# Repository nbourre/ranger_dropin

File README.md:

# Ranger drop-in: BEAPER Nano carrier for ESP32-S3

Goal: replace the Arduino-based **Makeblock Auriga** controller of an mBot Ranger with a custom carrier board for an **ESP32-S3-DevKitC-1-N16R8**, based on the mirobo.tech **BEAPER Nano** schematic converted to SMD parts (JLCPCB/LCSC, Basic parts where possible).

Project files: KiCad 10 (`Beaper-Esp32s3.kicad_sch`, `Beaper-Esp32s3.kicad_pcb`), custom footprint library `BEAPER-Nano.pretty`, custom symbol library `ESP32S3.kicad_sym`. Reference: `auriga/Me Auriga Schematic.pdf`.

> **Status (2026-10-22):** schematic and PCB are in sync (127 footprints, all on the top side so the board clips into the robot). **Placement is done; routing, ground pours and the final DRC are still to do.** See `memoire/notes-a-faire.md` for the layout, the decisions and the task list, and `memoire/MEMOIRE.md` for the working notes (Konnect MCP tips). Photos of the Auriga are in `auriga/photos/`; extra 3D models are in `3dmodels/`.

---

## 1. Makeblock Auriga (original controller)

Source: `auriga/Me Auriga Schematic.pdf` (one page, read as text). Items marked *(memory)* are not visible in that PDF and come from general knowledge of the mBot Ranger. The full pin-by-pin map is in [AURIGA_PINMAP.md](AURIGA_PINMAP.md).

**Board size (measured): 65.5 × 100 mm, corner radius 2 mm** (target outline for the drop-in PCB). The original has no mounting holes (clipped in).

| Function | Details |
|---|---|
| MCU | ATmega2560 *(memory)*, with ICSP header |
| USB-serial | CH340G |
| Motor driver | TB6612 (1.2 A continuous per channel), two motor ports with encoders (`ENC` signals, 51 Ω series resistors) |
| Motor power protection | Fuses (1 A per motor, 3.5 A main), SS54 diode, SMAJ TVS, 470 µF / 16 V on the motor rail |
| Regulators | 5 V LDO and 3.3 V XC6206 |
| IMU | MPU6050 gyroscope + accelerometer (I2C, INT and AD0 pins) |
| RGB LED ring | 12 RGB LEDs, one data line (`D44/RGB`) |
| Ambient light sensors | LIGHT1 and LIGHT2 |
| Sound sensor | Microphone with LM2904 amplifier |
| Temperature sensor | Present (`TEMP`) |
| Buzzer | Present |
| User button | One (`KEY`) |
| Status LEDs | LED_RED, LED_BLUE |
| RJ25 ports | 10 ports for Makeblock modules (line follower, ultrasonic, etc.) |
| Servo header | `P_SERVO`, powered from the motor rail (V-M) |
| Wireless | Bluetooth / 2.4 G module socket *(memory)* |

---

## 2. BEAPER Nano on ESP32-S3 (this project)

Carrier board for the ESP32-S3-DevKitC-1-N16R8 (U5, two 22-pin headers, 22.86 mm apart).

### Power
- Battery input on **J1** (5.5 × 2.1 mm DC barrel jack, centre = VBAT), 7.2 V NiMH RC pack. The old screw terminal CON1 was removed.
- Protection: the battery (net `VBAT`, SMAJ13A TVS D9) splits into two fused branches, as on the Auriga. **Motor branch:** fuse F1 (3.5 A), SS54 diode D8, 470 µF bulk capacitor C8, net `VCC` (TB6612 VM, battery sense, panel V-BAT). **Logic branch:** fuse F2 (3 A, C182445), SS34 diode D13, then the buck U1. A motor stall that blows F1 therefore leaves the logic and servos powered.
- **U1 (TPS54331DDA, 3 A buck, LCSC C90761)** makes the +5 V rail, as on the Auriga (L1 6.8 µH, D10 SS34, 10 k / 1.91 k feedback divider, 470 µF output capacitor). D11 (SS34) isolates the buck from the +5 V rail so that USB power cannot back-feed it (the rail is about 4.7 V), and D12 (SMAJ5.0A) clamps the rail. The DevKitC-1 has no VIN pin, so it is powered through its 5V pin. U1 is therefore **required**.
- 3.3 V comes from the DevKitC-1.
- No on-board USB charger (external charger for the pack).

### Motors
- **U3 TB6612FNG** (SSOP-24, LCSC C141517, Extended part). Replaces the SN754410 of the original design.
- Motor outputs are protected like on the Auriga: TB6612 output → bidirectional TVS SMAJ12CA (D14 to D17) → 120 Ω / 2 A ferrite bead (FB1 to FB4) → 1 A PTC fuse (F3 to F6) → connector.
- **M1 and M2** are **JST PH 6-pin side-entry connectors (2.0 mm pitch, S6B-PH-K)**, as on the Auriga (see `auriga/photos/`): pin 6 motor+, 5 motor−, 4 GND, 3 +3V3, 2 encoder A, 1 encoder B. Pin 1 orientation still has to be checked on a real motor plug.
- Encoder signals go through 51 Ω resistors (R31 to R34) to GPIO 39 to 42. Encoders are powered at **3.3 V** (the Auriga uses 5 V). To be tested with the real motors.
- Difference from the old driver: with both inputs low, the TB6612 coasts (the SN754410 braked). Maximum supply: 13.5 V.

### Sensors and I/O
- **U6 LSM6DS3TR-C** (LCSC C967633): 6-axis IMU on I2C (address 0x6A), interrupts not connected.
- **Battery voltage monitor** (`VOL_BAT`, like the Auriga's A4/VOL_BAT): R35 100 kΩ / R36 51 kΩ divider + C11 1 µF on **GPIO 3** (ADC1_CH2). Ratio 0.338, so a 9 V pack reads about 3.0 V. It is tapped after D8, so it reads about 0.4 V low: calibrate in firmware. GPIO 3 is a strapping pin, which only matters at reset.
- Ambient light sensor (TEPT4400) removed; the Auriga's light module will be reused instead (see TODO).
- Temperature sensor (MCP9700A, on A1), wired directly (no selection jumpers).
- Line / floor sensors and potentiometers were **removed** to free GPIO. As on the Auriga, line-following is done by an external I2C module (home-made: Adafruit ATtiny1616 with seesaw firmware, sensors wired to the ATtiny) on the Qwiic connector (J4) or H1/H4.
- Headers H1 (A4 / SDA) and H4 (A5 / SCL): I2C signals at 3.3 V. The sonar headers H2/H3 were removed.
- Headers H7 (A6 / GPIO 6) and H8 (A7 / GPIO 7): 5 V servo outputs through the **74HCT541** level shifter (U2) for the pan/tilt micro servos (H5/H6 removed). Generate the servo PWM with LEDC.
- I2C expansion on the main 3.3 V bus: two Qwiic / JST-SH connectors (J4, J8) and three generic 4-pin headers (J9, J15, J16: GND, +3V3, SCL, SDA). SPI / TFT connector (J3).
- Piezo buzzer (LS1), 4 status LEDs (D2 to D5), reset button (SW1).

### GPIO mapping (Arduino-style net name → ESP32-S3 GPIO)

| Net | GPIO | Net | GPIO |
|---|---|---|---|
| PA_S1 (RJ25 A) | 1 | D5 | 17 |
| A1 | 2 | D6 | 18 |
| A2 (LIGHT2) | 4 | D7 | 21 |
| A3 (LIGHT1) | 5 | D8 (buzzer) | 47 |
| A6 | 6 | D9 (J3, RJ25 C) | 38 |
| A7 | 7 | D10 (J3, RJ25 C) | 10 |
| A4/SDA | 8 | D11/COPI | 11 |
| A5/SCL | 9 | D12/CIPO | 13 |
| PB_S2 (RJ25 B) | 44 | D13/SCK | 12 |
| PB_S1 (RJ25 B) | 43 | ~{RST} (SW1) | EN |
| KEY_GPIO | 14 | Encoders | 39, 40, 41, 42 |
| PA_S2 (RJ25 A) | 15 | RGB_3V3 (ring data) | 48 |
| D4 | 16 | VOL_BAT | 3 |

No free GPIO is left. **45, 46, 0** are strapping pins (unused, usable with care). **19, 20** are USB D−/D+. **35, 36, 37** are used by the octal PSRAM and must stay unused. GPIO 43/44 are the UART0 pins of the DevKitC-1 USB-UART bridge: a module on RJ25 port B may conflict while that USB port is connected.

### Panel module, RJ25, Qwiic and expansion connectors
- **J12** PRGB (female 1x7, left to right): V-BAT (`VCC`), KEY, A2/LIGHT2, A3/LIGHT1, RGB, GND, 5 V. **J13, J14**: female 1x2 GND supports.
- **KEY** is active high: the module button ties KEY to V-BAT (measured with a multimeter). R38 15k / R37 10k to GND divide it to under 3.4 V on GPIO 14. Configure GPIO 14 as input with no internal pull-up.
- **RGB ring data:** GPIO 48 → U7 74AHCT1G125 (3.3 V → 5 V buffer) → R39 220 Ω → J12.5.
- **J5, J6, J7** RJ25 (Amphenol 54601-906WPLF, 6P6C), low-power side only: 1 SCL, 2 SDA, 3 GND, 4 +5 V, 5 S1, 6 S2. They behave like the Auriga ports (**5 V**): the six S1/S2 signals go through BSS138 level shifters (Q3 to Q8, 10 k pull-ups R45 to R56), and the port supply is `5V_P` (buck output before D11). The RJ25 I2C bus (EXT_SCL / EXT_SDA, through Q1/Q2) has its pull-ups on 3.3 V or 5 V, selected with **JP1** (1-2 = 3.3 V, 2-3 = 5 V, Makeblock setting). Digital only (no 0–5 V analog); port B uses GPIO 43/44 (UART0); port C shares D9/D10 with the SPI header J3. The jacks have the contacts on top (the Auriga's are at the bottom): the cable just has to be twisted, the pinout is the same.
- **J4, J8** Qwiic (JST-SH 4-pin: GND, 3V3, SDA, SCL); **J9, J15, J16** generic I2C headers.
- **J10** VL53L1X module (Amazon board, silkscreen order): 1 VIN (3.3 V), 2 GND, 3 SCL, 4 SDA, 5 GPIO1 (not connected), 6 XSHUT (not connected). On placement it must point the same way as the Auriga motor connectors.
- **J11** OLED I2C socket, assumed order GND, 3V3, SCL, SDA (module not yet chosen, to confirm).

---

## 3. Comparison

### On the Auriga but missing on the new board
- 12-LED ring itself and the light sensors: the Auriga **panel module is reused** through J12 to J14 (the ring data line is level-shifted from GPIO 48).
- Microphone and amplifier.
- Power switch.
- RJ25 ports: only 3 low-power ports (J5 to J7) are provided, no motor-power side.
- Dedicated Bluetooth / 2.4 G socket. Wi-Fi and BLE are built into the ESP32-S3.

### On the new board but not on the Auriga
- SPI / TFT connector (J3).
- Qwiic / JST-SH I2C connectors (J4, J8) and generic I2C headers (J9, J15, J16).
- VL53L1X module socket (J10) and OLED I2C socket (J11).
- I2C headers H1 / H4 (3.3 V) and servo headers H7 / H8 (5 V outputs).
- Onboard user buttons were removed; the user button is planned on the panel module `KEY` pin (see TODO).
- Four simple status LEDs.
- Wi-Fi and BLE through the ESP32-S3, with native USB.

### In both
Buzzer, temperature sensor, IMU, battery voltage sensing, motors with encoders, battery protection, reset button, servo outputs.

---

## 4. Open items
- **5 V supply:** done. The LM2940 was replaced by a TPS54331 3 A buck, and C7 (470 µF) sits near the servo headers. Use 5 V micro servos (9 g) and generate the servo signals with LEDC. The buck has its own fuse F2 and reverse diode D13, separate from the motor fuse F1. The motor outputs have their own TVS, ferrite and 1 A PTC fuse (done).
- The DevKitC-1 footprint outline is approximate (pad envelope only), and it has no 3D model yet.
- Missing LCSC references: F1, D8, D9, C8 (470 µF probably not stocked), R31 to R36, R45 to R56, C9 to C12, M1/M2 (S6B-PH-K-S), U7, RJ25, Qwiic. The 5.62 kΩ and 1.37 kΩ resistors are Extended only.
- Routing, ground pours, silkscreen clean-up and the final DRC are not done. The motor lines are long (U3 near the top, M1/M2 at the bottom edge).
- Missing 3D models: L1 (Bourns SRP7028A), SW1 (Alps SKRTLAE010), U5, G1. The RJ25 model is in `3dmodels/`.
- Optional additions to match the Auriga: power switch.
- The title block comment 3 still says "for Arduino Nano ESP32".
- The schematic page was enlarged from B to C to make room for the IMU.
- ERC: 0 errors, 58 warnings (library symbol mismatches, missing `Conn_01x03_Male`, `ARPS` and `UBMP4.1-rescue` libraries, same local/global label names, one U6 SDO pin type conflict). Leftover wires, orphan power symbols and floating labels were cleaned.

---

## 5. TODO
- [x] **Distance sensor** VL53L1X: socket J10 on the I2C bus (Amazon module, order VIN, GND, SCL, SDA, GPIO1, XSHUT; last two not connected). Must face the same way as the Auriga motor connectors at placement.
- [x] **Auriga panel module** (RGB ring + light sensors): J12 (1x7 female), J13/J14 (1x2 GND supports), level-shifted data (U7). See `AURIGA_PINMAP.md` for the geometry to reproduce at placement (module 36.1 × 50 mm, GND headers 31.75 mm apart).
- [x] Panel KEY used as the general button (active high, divider to GPIO 14). Board buttons SW2 to SW5 removed.
- [x] 3 RJ25 ports (low-power side, 5 V with level shifters), 2 Qwiic connectors and 3 generic I2C headers.
- [x] PCB outline (65.5 × 100 mm, R2) and the three Ø 2 mm guide holes.
- [x] `update_pcb_from_schematic` and component placement (everything on the top side).
- [ ] Routing, ground pours, silkscreen clean-up, final ERC / DRC, 3D check.
- [ ] **Mount the DevKit (U5) on "double" female headers: 2x22 instead of 1x22 per side.** One row receives the DevKit pins, the parallel extra row (wired pin to pin, preferably on the outer side) gives access to every DevKit pin for measurements, jumper wires and other DevKit variants. Likely a custom U5 footprint with two pads per pin number. Check the width (22.86 mm + 2 × 2.54 mm on a 65.5 mm board), the neighbours (J3, J11, the H column) and the height budget under the panel module (about 8.5 mm). Do this first: it makes the next item mostly unnecessary.
- [ ] **Breakout header for GPIO 35, 36 and 37.** These pins are reserved by the **octal PSRAM** ("R8" variants: N16R8, N8R8), whatever the flash size. They are free on variants without octal PSRAM that share the same footprint (N8R2 with quad PSRAM, N8 / N4 without PSRAM), so a 1x03 header would only be useful with one of those (to be confirmed against the Espressif module datasheet). Label it on the silkscreen ("without octal PSRAM only") and update the GPIO table if used.
- [ ] Confirm the OLED module pinout (J11 is an assumed order).
- [ ] LCSC references for the new parts (connectors, U7, R37 to R39, C12).
- [ ] Line-follower I2C module (home-made, Adafruit ATtiny1616 with seesaw, address 0x49) on a Qwiic connector. Source: `nbourre/LyneTracker` (target ATmega2560; porting only needs the I2C pins GPIO 8/9, 3.3 V). Check pull-ups and supply at 3.3 V.
- [ ] **Makeblock mounting holes:** nominally 8 mm pitch, M4; measure on a real beam.

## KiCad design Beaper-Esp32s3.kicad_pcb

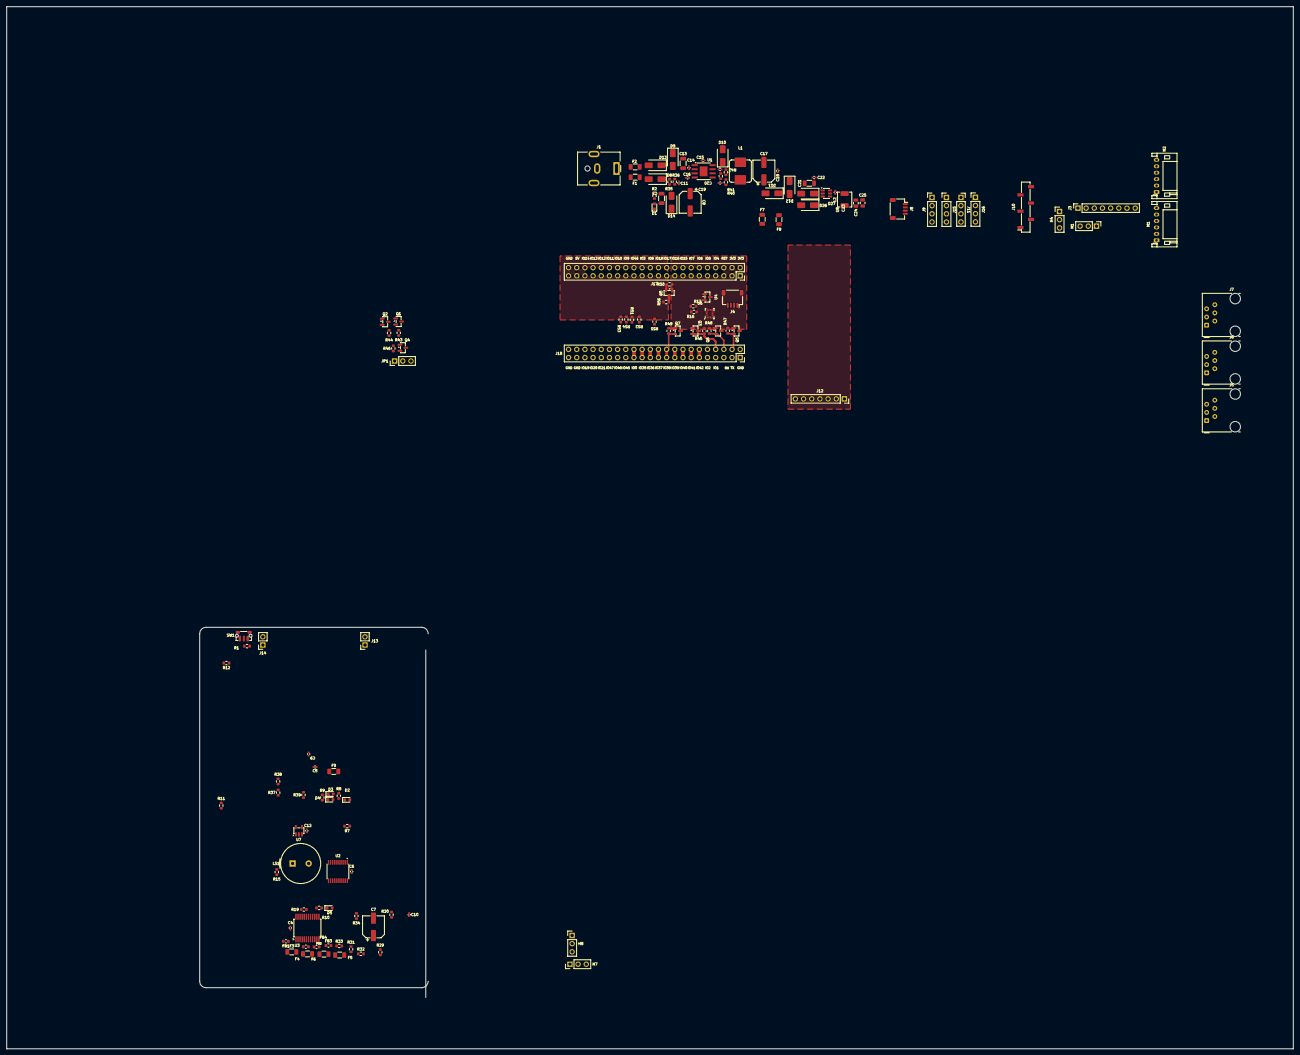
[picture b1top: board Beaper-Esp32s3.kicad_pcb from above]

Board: 2 copper layers, 399.9 x 323.9 mm, 133 parts (0 on the bottom side), 104 nets.

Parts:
C3, C13, C21: 10uF/50V; C_1206_3216Metric
C4, C5, C6, C9, C10, C12, C14, C15, C18, C22, C23: 100nF; C_0402_1005Metric
C7, C8: 470uF/16V; CP_Elec_6.3x7.7
C11: 1uF; C_0402_1005Metric
C16: 10nF; C_0402_1005Metric
C17: 470uF; CP_Elec_6.3x7.7
C19: 120pF; C_0402_1005Metric
C20: 68pF; C_0402_1005Metric
C24, C25: 22uF/10V; C_0805_2012Metric
D1: Vin; LED_0603_1608Metric
D2, D3, D4, D5: LED; LED_0603_1608Metric
D8, D10, D11: SS54; D_SMA
D9: SMAJ13CA; D_SMA
D12: SMAJ5.0CA; D_SMA
D13, D26, D27: SS34; D_SMA
D14: SMAJ10CA; D_SMA
F1: 4A T; Fuse_1206_3216Metric
F2: 3A; Fuse_1206_3216Metric
F3, F4, F5, F6, F9: 1A PTC; Fuse_1206_3216Metric
F7: 1.5A PTC; Fuse_1206_3216Metric
F8: 1.1A PTC; Fuse_1206_3216Metric
FB1, FB2, FB3, FB4: 120R/2A; L_0603_1608Metric
H1: A4 (SDA); PinHeader_1x03_P2.54mm_Vertical
H4: A5 (SCL); PinHeader_1x03_P2.54mm_Vertical
H7: A6 (Servo 3); PinHeader_1x03_P2.54mm_Vertical
H8: A7 (Servo 4); PinHeader_1x03_P2.54mm_Vertical
J1: PJ-063AH 8A (2,0 mm); BarrelJack_CUI_PJ-063AH_Horizontal
J3: Conn_01x08; PinSocket_1x08_P2.54mm_Vertical
J4, J8: QWIIC/JST SH; JST_SH_SM04B-SRSS-TB_1x04-1MP_P1.00mm_Horizontal
J5: RJ25 port A; RJ12_Amphenol_54601-x06_Horizontal
J6: RJ25 port B; RJ12_Amphenol_54601-x06_Horizontal
J7: RJ25 port C; RJ12_Amphenol_54601-x06_Horizontal
J9, J15, J16: I2C (GND 3V3 SCL SDA); PinHeader_1x04_P2.54mm_Vertical
J10: VL53L1X module; PinSocket_1x06_P2.54mm_Vertical_SMD_Pin1Right
J11: OLED I2C; PinSocket_1x04_P2.54mm_Vertical
J12: PRGB (Auriga panel module); PinSocket_1x07_P2.54mm_Vertical
J13: PG1 (GND support); PinSocket_1x02_P2.54mm_Vertical
J14: PG2 (GND support); PinSocket_1x02_P2.54mm_Vertical
J17: Socket 2x22 (U5 L1-L22); PinSocket_2x22_P2.54mm_Vertical
J18: Socket 2x22 (U5 R1-R22); PinSocket_2x22_P2.54mm_Vertical
JP1: I2C EXT 3V3/5V; PinHeader_1x03_P2.54mm_Vertical
L1: 6.8uH/4.5A; L_Bourns_SRP7028A_7.3x6.6mm
L2: 3.9uH; L_Sunlord_MWSA0412S
LS1: Piezo Beeper; Buzzer_TDK_PS1240P02BT_D12.2mm_H6.5mm
M1: Moteur 1 (MHDR1X6); JST_PH_S6B-PH-K_1x06_P2.00mm_Horizontal
M2: Moteur 2 (MHDR1X6); JST_PH_S6B-PH-K_1x06_P2.00mm_Horizontal
Q1, Q2, Q3, Q4, Q5, Q6, Q7, Q8: BSS138; SOT-23
R1: 100; R_0603_1608Metric
R2, R15: 1k0; R_0603_1608Metric
R7, R8, R9, R10: 270; R_0603_1608Metric
R11, R12: 150; R_0603_1608Metric
R16, R17: 4k7; R_0603_1608Metric
R19, R37, R45, R46, R47, R48, R49, R50, R51, R52, R53, R54, R55, R56: 10k; R_0603_1608Metric
R29, R30: 470; R_0603_1608Metric
R31, R32, R33, R34: 51; R_0603_1608Metric
R35: 100k; R_0603_1608Metric
R36: 51k; R_0603_1608Metric
R38: 15k; R_0603_1608Metric
R39: 330; R_0603_1608Metric
R40: 27k; R_0603_1608Metric
R41: 5.1k; R_0603_1608Metric
R42: 30k; R_0603_1608Metric
R43, R44: 4.7k; R_0603_1608Metric
SW1: RESET; SW_Push_1P1T-MP_NO_Horizontal_Alps_SKRTLAE010
U1: TPS54331DDA; TI_SO-PowerPAD-8
U2: 74HCT541; TSSOP-20_4.4x6.5mm_P0.65mm
U3: TB6612FNG; SSOP-24_5.3x8.2mm_P0.65mm
U4: MCP9700AT-E/TT; SOT-23
U6: LSM6DSOTR; LGA-14_3x2.5mm_P0.5mm_LayoutBorder3x4y
U7: 74AHCT1G125; SOT-23-5
U8: AP63203WU; TSOT-23-6

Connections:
+3V3: C5.1, C9.1, C10.1, J4.2, J17.1, J17.2, J17.3, J17.4, JP1.1, Q1.1 (G), Q2.1 (G), Q3.1 (G), Q4.1 (G), Q5.1 (G), Q6.1 (G), Q7.1 (G), Q8.1 (G), R16.1, R17.1, R45.2, R46.2, R47.2, R48.2, R49.2, R50.2, U4.1 (V_{DD}), U6.5 (VDDIO), U6.8 (VDD), U6.12 (CS)
+3V3_EXT: C24.1, C25.1, H1.2, H4.2, J3.2, J8.2, J9.2, J10.1, J11.2, J15.2, J16.2, L2.2, M1.3, M2.3, U8.1 (FB)
+5V: C4.1, C6.1, C12.1, D11.1 (K), D12.2 (A2), D27.2 (A), F7.1, F8.1, J17.41, J17.42, JP1.3, R19.1, R51.1, R52.1, R53.1, R54.1, R55.1, R56.1, U2.20 (VCC), U3.15 (PWMB), U3.20 (VCC), U3.23 (PWMA), U7.5 (VCC)
+5V_EXT: F8.2, J5.4, J6.4, J7.4, J12.7
+5V_SERVO: C7.1, F7.2, H7.2, H8.2
/A1: J18.9, J18.10, U4.2 (V_{OUT})
/A2: J12.3, J17.7, J17.8
/A3: J12.4, J17.9, J17.10
/A4/SDA: J4.3, J8.3, J9.4, J10.4, J11.4, J15.4, J16.4, J17.23, J17.24, Q1.2 (S), R11.2, R16.2, U2.5 (A3), U6.14 (SDA)
/A5/SCL: J4.4, J8.4, J9.3, J10.3, J11.3, J15.3, J16.3, J17.29, J17.30, Q2.2 (S), R12.2, R17.2, U2.4 (A2), U6.13 (SCL)
/A6: J17.11, J17.12, U2.3 (A1)
/A7: J17.13, J17.14, U2.2 (A0)
/BUCK_BST: C23.1, U8.6 (BST)
/BUCK_SW: C23.2, L2.1, U8.5 (SW)
/D4: J17.17, J17.18, R7.1, U2.6 (A4)
/D5: J17.19, J17.20, R8.1, U2.7 (A5)
/D6: J17.21, J17.22, R9.1, U2.8 (A6)
/D7: J18.35, J18.36, R10.1, U2.9 (A7)
/D8: J18.33, J18.34, LS1.1, R15.2
/D9: J3.6, J18.19, J18.20, Q7.2 (S), R49.1
/D10: J3.7, J17.31, J17.32, Q8.2 (S), R50.1
/D11/COPI: J3.4, J17.33, J17.34
/D12/CIPO: J3.8, J17.37, J17.38
/D13/SCK: J3.3, J17.35, J17.36
/ENC1A: J18.17, J18.18, R31.2
/ENC1A_H: M1.2, R31.1
/ENC1B: J18.15, J18.16, R32.2
/ENC1B_H: M1.1, R32.1
/ENC2A: J18.13, J18.14, R33.2
/ENC2A_H: M2.2, R33.1
/ENC2B: J18.11, J18.12, R34.2
/ENC2B_H: M2.1, R34.1
/EXT_SCL: J5.1, J6.1, J7.1, Q2.3 (D), R44.2
/EXT_SDA: J5.2, J6.2, J7.2, Q1.3 (D), R43.2
/FB: R40.2, R41.1, U1.5 (VSENSE)
/IMU_INT1: J17.27, J17.28, U6.4 (INT1)
/KEY: J12.2, R38.1
/KEY_GPIO: J17.39, J17.40, R37.2, R38.2
/M1A: F3.2, M1.6
/M1A_D: FB1.1, U3.1 (AO1), U3.2 (AO1)
/M1B: F4.2, M1.5
/M1B_D: FB2.1, U3.5 (AO2), U3.6 (AO2)
/M1_IN1: U2.14 (Y4), U3.21 (AIN1)
/M1_IN2: U2.13 (Y5), U3.22 (AIN2)
/M2A: F5.2, M2.6
/M2A_D: FB3.1, U3.11 (BO1), U3.12 (BO1)
/M2B: F6.2, M2.5
/M2B_D: FB4.1, U3.7 (BO2), U3.8 (BO2)
/M2_IN1: U2.12 (Y6), U3.17 (BIN1)
/M2_IN2: U2.11 (Y7), U3.16 (BIN2)
/MOTOR_STBY: R19.2, U3.19 (STBY)
/PA_S1: J18.7, J18.8, Q3.2 (S), R45.1
/PA_S1_5V: J5.5, Q3.3 (D), R51.2
/PA_S2: J17.15, J17.16, Q4.2 (S), R46.1
/PA_S2_5V: J5.6, Q4.3 (D), R52.2
/PB_S1: J18.3, J18.4, Q5.2 (S), R47.1
/PB_S1_5V: J6.5, Q5.3 (D), R53.2
/PB_S2: J18.5, J18.6, Q6.2 (S), R48.1
/PB_S2_5V: J6.6, Q6.3 (D), R54.2
/PC_S1_5V: J7.5, Q7.3 (D), R55.2
/PC_S2_5V: J7.6, Q8.3 (D), R56.2
/RGB: J12.5, R39.2
/RGB_3V3: J18.31, J18.32, U7.2
/RGB_BUF: R39.1, U7.4
/VBAT_IN: F1.2, F2.1, J1.1
/VBUCK: C21.1, C22.1, D26.1 (K), D27.1 (K), U8.2 (EN), U8.3 (IN)
/VI2C: JP1.2, R43.1, R44.1
/VOL_BAT: C11.1, J17.25, J17.26, R35.2, R36.1
/~RST: J3.5, J17.5, J17.6, R1.2
GND: C3.2, C4.2, C5.2, C6.2, C7.2, C8.2, C9.2, C10.2, C11.2, C12.2, C13.2, C14.2, C16.2, C17.2, C18.2, C19.2, C20.2, C21.2, C22.2, C24.2, C25.2, D1.1 (K), D2.1 (K), D3.1 (K), D4.1 (K), D5.1 (K), D9.1 (A1), D10.2 (A), D12.1 (A1), D14.1 (A1), H1.3, H4.3, H7.3, H8.3, J1.2, J3.1, J4.1, J5.3, J6.3, J7.3, J8.1, J9.1, J10.2, J11.1, J12.6, J13.1, J13.2, J14.1, J14.2, J15.1, J16.1, J17.43, J17.44, J18.1, J18.2, J18.41, J18.42, J18.43, J18.44, LS1.2, M1.4, M2.4, R15.1, R36.2, R37.1, R41.2, SW1.1, U1.7 (GND), U1.9 (PowerPAD), U2.1 (G1), U2.10 (GND), U2.19 (G2), U3.3 (PGND1), U3.4 (PGND1), U3.9 (PGND2), U3.10 (PGND2), U3.18 (GND), U4.3 (GND), U6.1 (SDO/SA0), U6.2 (SDX), U6.3 (SCX), U6.6 (GND), U6.7 (GND), U7.1, U7.3 (GND), U8.4 (GND)
unnamed: C19.1, R42.2
unnamed: D1.2 (A), R2.1
unnamed: D2.2 (A), R7.2
unnamed: D3.2 (A), R8.2
unnamed: D4.2 (A), R9.2
unnamed: D5.2 (A), R10.2
unnamed: D8.2 (A), F1.1
unnamed: C15.2, D10.1 (K), L1.1, U1.8 (PH)
unnamed: C17.1, C18.1, D11.2 (A), L1.2, R40.1
unnamed: D13.2 (A), F2.2
unnamed: C13.1, C14.1, D9.2 (A2), D13.1 (K), U1.2 (VIN)
unnamed: F3.1, FB1.2
unnamed: F4.1, FB2.2
unnamed: F5.1, FB3.2
unnamed: F6.1, FB4.2
unnamed: H1.1, R11.1
unnamed: H4.1, R12.1
unnamed: H7.1, R29.1
unnamed: H8.1, R30.1
unnamed: J18.21, J18.22
unnamed: J18.23, J18.24
unnamed: J18.25, J18.26
unnamed: J18.27, J18.28
unnamed: J18.29, J18.30
unnamed: J18.37, J18.38
unnamed: J18.39, J18.40
unnamed: R1.1, SW1.2
unnamed: C15.1, U1.1 (BOOT)
unnamed: C20.1, R42.1, U1.6 (COMP)
unnamed: C16.1, U1.4 (SS/TR)
unnamed: R30.2, U2.18 (Y0)
unnamed: R29.2, U2.17 (Y1)
VCC: C3.1, C8.1, D8.1 (K), D14.2 (A2), D26.2 (A), F9.1, R2.2, R35.1, U3.13 (VM2), U3.14 (VM3), U3.24 (VM1)
VCC_EXT: F9.2, J12.1

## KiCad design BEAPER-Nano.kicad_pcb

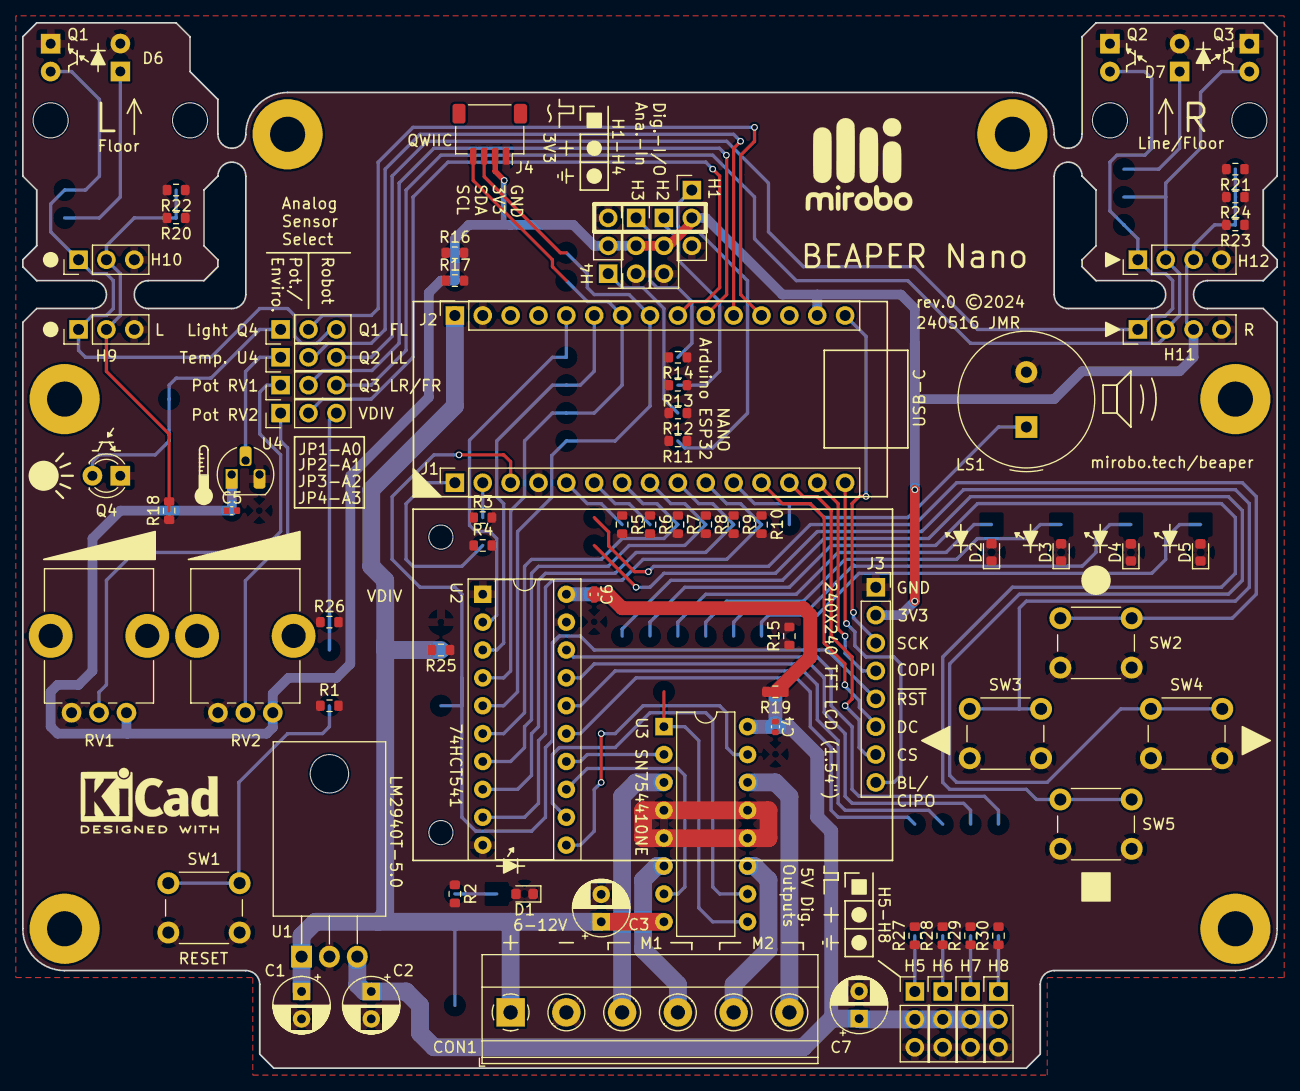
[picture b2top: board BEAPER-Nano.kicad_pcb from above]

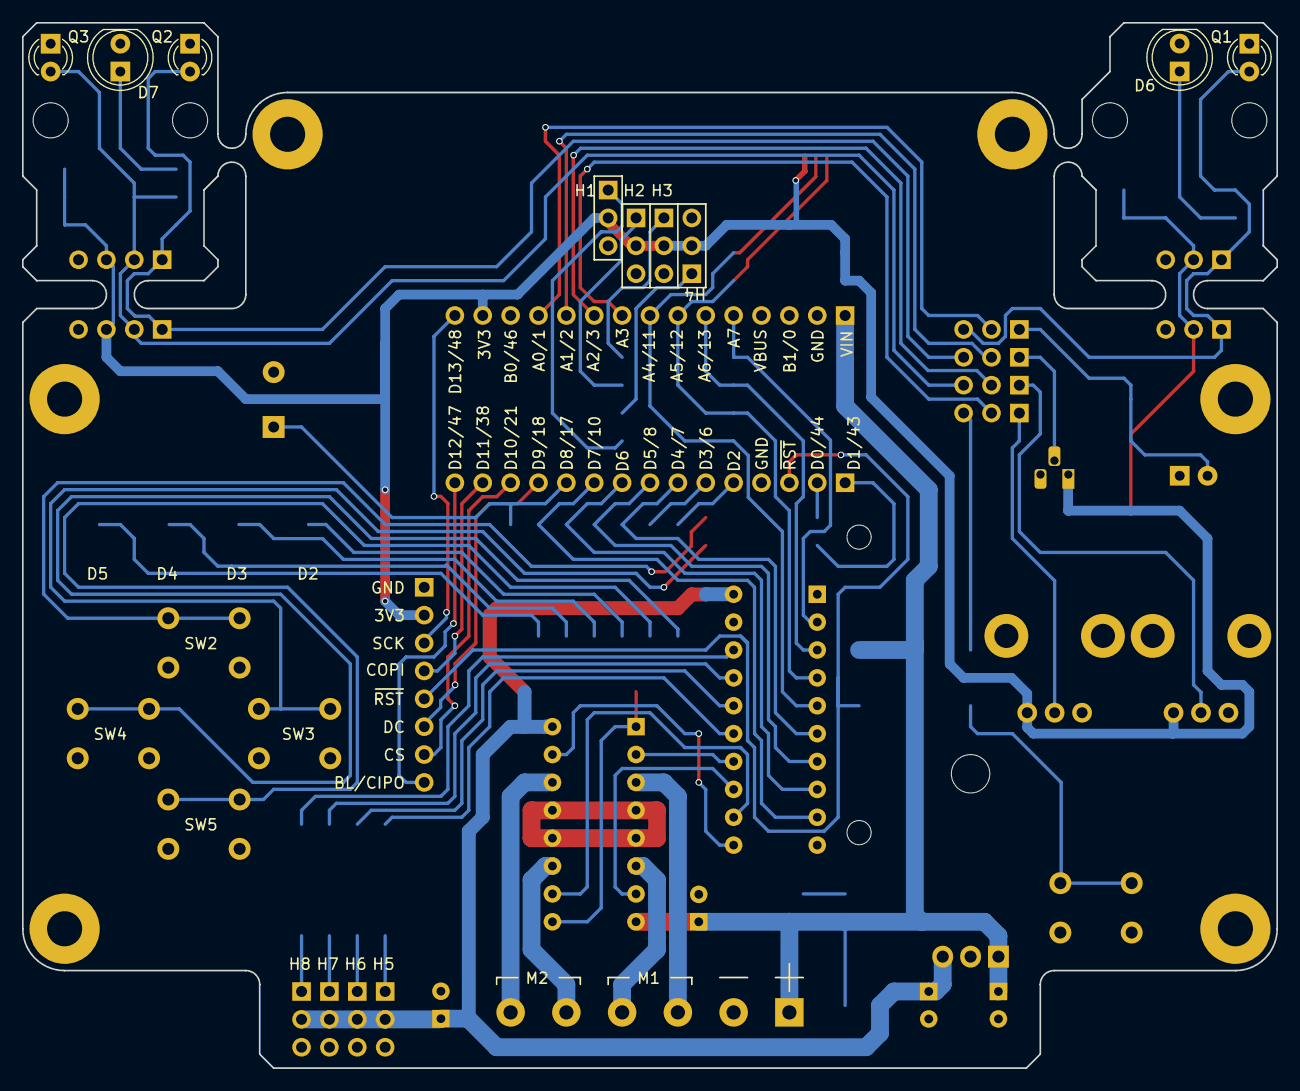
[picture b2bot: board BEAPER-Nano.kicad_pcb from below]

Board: 2 copper layers, 114.3 x 95.2 mm, 82 parts (5 on the bottom side), 68 nets.

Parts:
C1, C2, C3, C7: 10uF; CP_Radial_D5.0mm_P2.50mm
C4, C5, C6: 100nF; C_0402_1005Metric
CON1: Phoenix 1729160; TerminalBlock_Phoenix_MKDS-1,5-6-5.08_1x06_P5.08mm_Horizont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
D1: Vin; LED_0603_1608Metric
D2, D3, D4, D5: LED; LED_0603_1608Metric
D6, D7: OED-EL-1L2; LED_D5.0mm_Clear
G1: mirobotech_logo; mirobo_logo_10
H1: A4 (SDA); PinHeader_1x03_P2.54mm_Vertical
H2: A6 (SONAR TRIG); PinHeader_1x03_P2.54mm_Vertical
H3: A7 (SONAR ECHO); PinHeader_1x03_P2.54mm_Vertical
H4: A5 (SCL); PinHeader_1x03_P2.54mm_Vertical
H5: A4 (Servo 1); PinHeader_1x03_P2.54mm_Vertical
H6: A5 (Servo 2); PinHeader_1x03_P2.54mm_Vertical
H7: A6 (Servo 3); PinHeader_1x03_P2.54mm_Vertical
H8: A7 (Servo 4); PinHeader_1x03_P2.54mm_Vertical
H9, H10: Conn_01x03_Male; PinHeader_1x03_P2.54mm_Vertical
H11, H12: Conn_01x04_Pin; PinHeader_1x04_P2.54mm_Vertical
J1: Digital; PinSocket_1x15_P2.54mm_Vertical
J2: Analog; PinSocket_1x15_P2.54mm_Vertical
J3: Conn_01x08; PinSocket_1x08_P2.54mm_Vertical
J4: QWIIC/JST SH; JST_SH_SM04B-SRSS-TB_1x04-1MP_P1.00mm_Horizontal
JP1, JP2: ALS/LFS; PinHeader_1x03_P2.54mm_Vertical
JP3, JP4: POT/VDIV; PinHeader_1x03_P2.54mm_Vertical
LS1: Piezo Beeper; Buzzer_TDK_PS1240P02BT_D12.2mm_H6.5mm
Q1, Q2, Q3: LTR-4206E; LED_D3.0mm_IRBlack
Q4: TEPT4400; LED_D3.0mm_Clear
R1, R11, R12, R13, R14, R20, R21, R27, R28, R29, R30: 100; R_0603_1608Metric
R2, R3, R4, R5, R6, R15: 1k0; R_0603_1608Metric
R7, R8, R9, R10: 270; R_0603_1608Metric
R16, R17, R18, R22, R23, R24: 4k7; R_0603_1608Metric
R19: 10k; R_0603_1608Metric
R25: 5.62k-1%; R_0603_1608Metric
R26: 1.37k-1%; R_0603_1608Metric
RV1, RV2: 10k; Potentiometer_Bourns_PTV09A-1_Single_Vertical
SW1: RESET; SW_PUSH_6mm
SW2, SW3, SW4, SW5: SW_Push; SW_PUSH_6mm
U1: LM2940T-5.0; TO-220-3_Horizontal_TabDown
U2: 74HCT541; DIP-20_W7.62mm_Socket
U3: SN754410NE; DIP-16_W7.62mm
U4: MCP9700A-E/TO; TO-92_HandSolder

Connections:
+3V3: C5.1, H1.2, H2.2, H3.2, H4.2, H9.2, H10.2, H11.3, H12.3, J2.14, J3.2, J4.2, R16.1, R17.1, R18.1, R20.1, R21.1, R22.1, R23.1, R24.1, RV1.1, RV2.1, U4.1 (V_{DD})
+5V: C2.1, C4.1, C6.1, C7.1, H5.2, H6.2, H7.2, H8.2, R19.1, U1.3 (VO), U2.20 (VCC), U3.16 (VCC1)
/A0: J2.12, JP1.2 (C)
/A1: J2.11, JP2.2 (C)
/A2: J2.10, JP3.2 (C)
/A3: J2.9, JP4.2 (C)
/A4/SDA: J2.8, J4.3, R11.2, R16.2, U2.5 (A3)
/A5/SCL: J2.7, J4.4, R12.2, R17.2, U2.4 (A2)
/A6: J2.6, R13.2, U2.3 (A1)
/A7: J2.5, R14.2, U2.2 (A0)
/D0/RX0: J1.2, R3.1
/D1/TX0: J1.1, R4.1
/D2: J1.5, R5.1
/D3: J1.6, R6.1
/D4: J1.7, R7.1, U2.6 (A4)
/D5: J1.8, R8.1, U2.7 (A5)
/D6: J1.9, R9.1, U2.8 (A6)
/D7: J1.10, R10.1, U2.9 (A7)
/D8: J1.11, LS1.1, R15.2
/D9: J1.12, J3.6
/D10: J1.13, J3.7
/D11/COPI: J1.14, J3.4
/D12/CIPO: J1.15, J3.8
/D13/SCK: J2.15, J3.3
/Q1: H9.1, H10.1, JP1.3 (B), Q1.1 (C), R22.2
/Q2: H11.1, H12.1, JP2.3 (B), Q2.1 (C), R23.2
/Q3: H11.2, H12.2, JP3.3 (B), Q3.1 (C), R24.2
/~RST: J1.3, J3.5, R1.2
GND: C1.2, C2.2, C3.2, C4.2, C5.2, C6.2, C7.2, CON1.2, D1.1 (K), D2.1 (K), D3.1 (K), D4.1 (K), D5.1 (K), D6.1 (K), D7.1 (K), H1.3, H2.3, H3.3, H4.3, H5.3, H6.3, H7.3, H8.3, H9.3, H10.3, H11.4, H12.4, J1.4, J2.2, J3.1, J4.1, LS1.2, Q1.2 (E), Q2.2 (E), Q3.2 (E), Q4.2 (E), R15.1, R26.2, RV1.3, RV2.3, SW1.1, SW2.1, SW3.1, SW4.1, SW5.1, U1.2 (GND), U2.1 (G1), U2.10 (GND), U2.19 (G2), U3.4 (GND), U3.5 (GND), U3.12 (GND), U3.13 (GND), U4.3 (GND)
unnamed: CON1.3, U3.3 (1Y)
unnamed: CON1.4, U3.6 (2Y)
unnamed: CON1.5, U3.11 (3Y)
unnamed: CON1.6, U3.14 (4Y)
unnamed: D1.2 (A), R2.1
unnamed: D2.2 (A), R7.2
unnamed: D3.2 (A), R8.2
unnamed: D4.2 (A), R9.2
unnamed: D5.2 (A), R10.2
unnamed: D6.2 (A), R20.2
unnamed: D7.2 (A), R21.2
unnamed: H1.1, R11.1
unnamed: H2.1, R13.1
unnamed: H3.1, R14.1
unnamed: H4.1, R12.1
unnamed: H5.1, R27.1
unnamed: H6.1, R28.1
unnamed: H7.1, R29.1
unnamed: H8.1, R30.1
unnamed: JP1.1 (A), Q4.1 (C), R18.2
unnamed: JP2.1 (A), U4.2 (V_{OUT})
unnamed: JP3.1 (A), RV1.2
unnamed: JP4.1 (A), RV2.2
unnamed: JP4.3 (B), R25.2, R26.1
unnamed: R1.1, SW1.2
unnamed: R3.2, SW2.2
unnamed: R4.2, SW3.2
unnamed: R5.2, SW4.2
unnamed: R6.2, SW5.2
unnamed: R30.2, U2.18 (Y0)
unnamed: R29.2, U2.17 (Y1)
unnamed: R28.2, U2.16 (Y2)
unnamed: R27.2, U2.15 (Y3)
unnamed: U2.14 (Y4), U3.2 (1A)
unnamed: U2.13 (Y5), U3.7 (2A)
unnamed: U2.12 (Y6), U3.10 (3A)
unnamed: U2.11 (Y7), U3.15 (4A)
unnamed: R19.2, U3.1 (1,2EN), U3.9 (3,4EN)
VCC: C1.1, C3.1, CON1.1, J2.1, R2.2, R25.1, U1.1 (VI), U3.8 (VCC2)

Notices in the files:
BEAPER-Nano.kicad_pcb:
©2024 mirobo.tech
rev.0 ©2024
